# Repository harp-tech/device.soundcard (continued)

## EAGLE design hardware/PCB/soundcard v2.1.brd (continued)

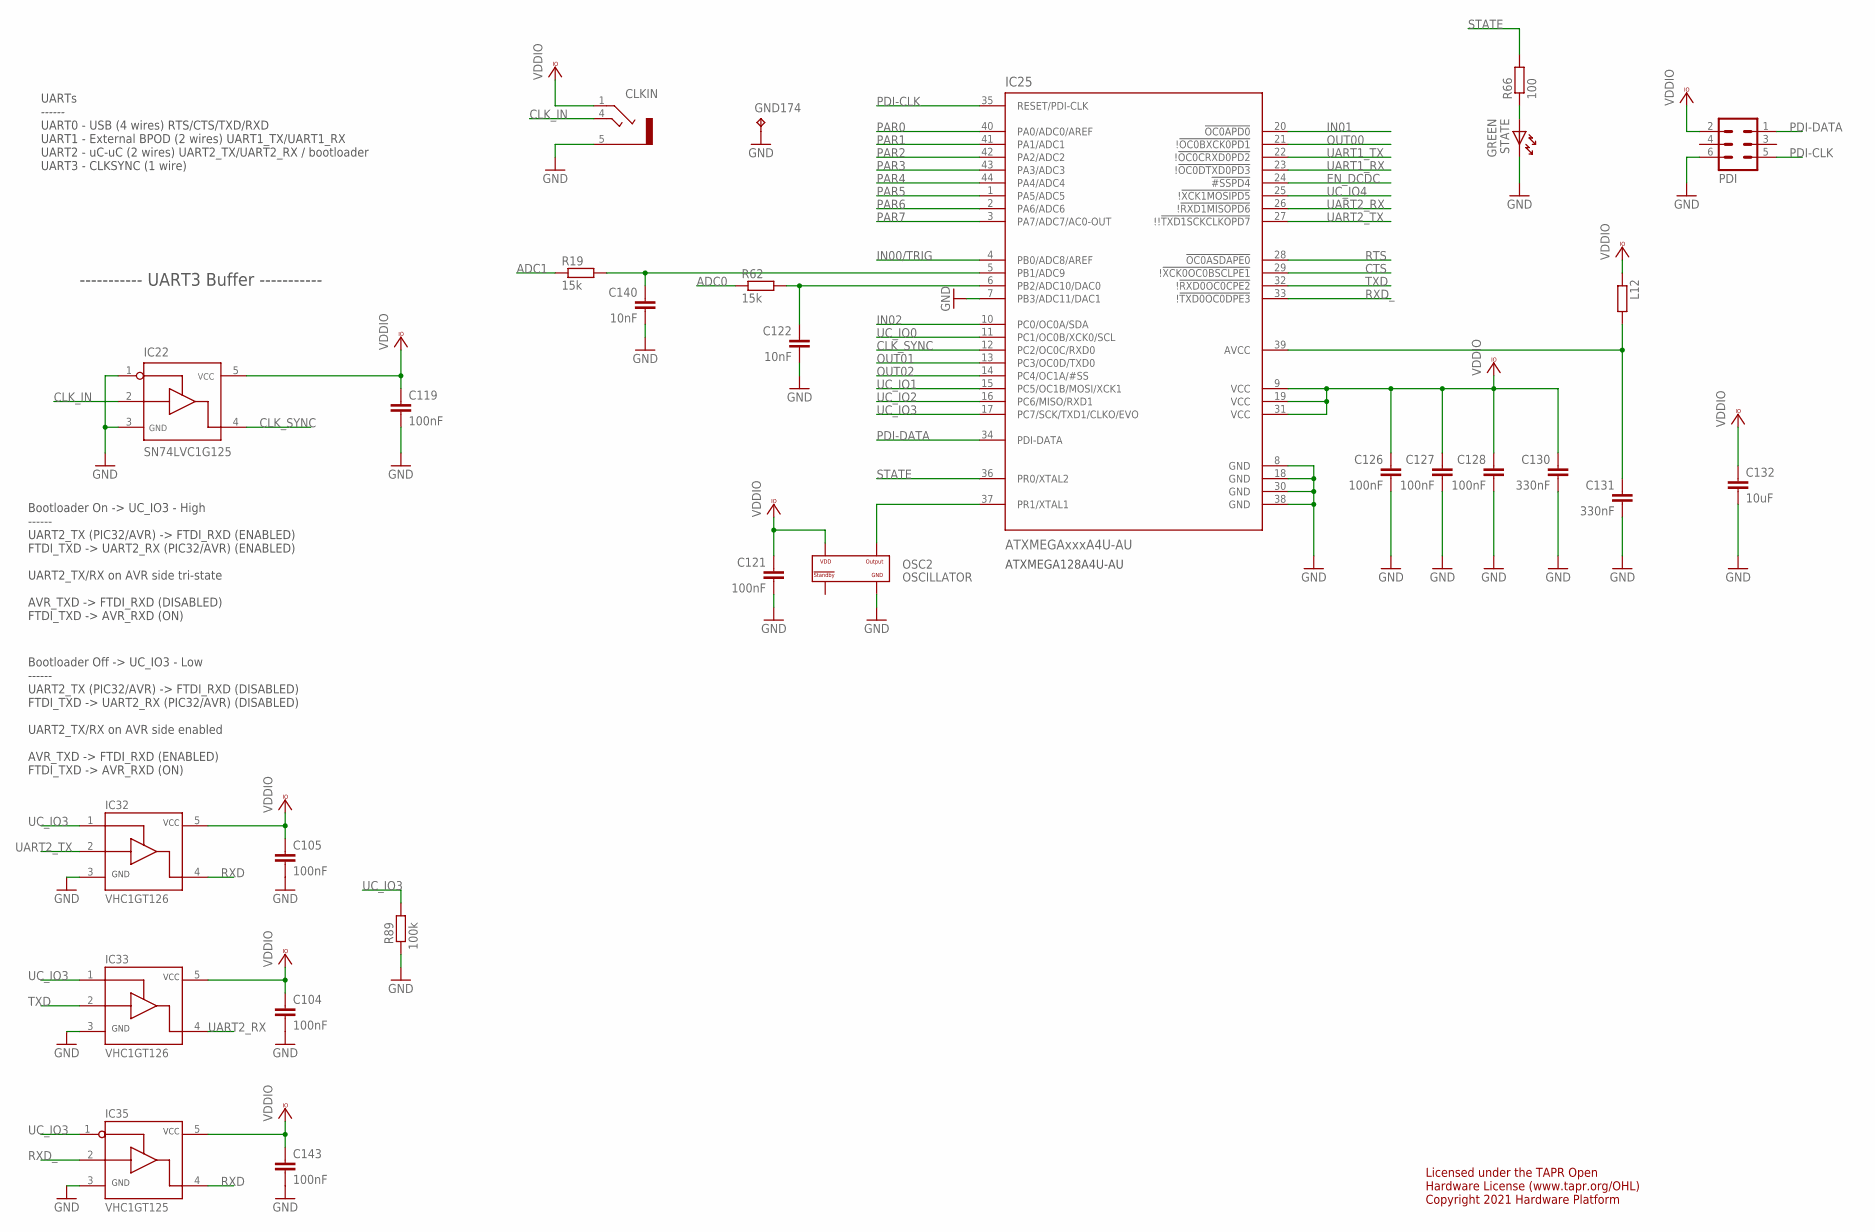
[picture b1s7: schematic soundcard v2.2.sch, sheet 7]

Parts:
C104, C105, C119, C121, C126, C127, C128, C143: 100nF; C0402
C122, C140: 10nF; C0402
C130, C131: 330nF; C0402
C132: 10uF; C0603
CLKIN: STEREO_JACK; 35RASMT2BHNTRX
GND174: TP; TP_1
IC22: SN74LVC1G125; SOT23-5
IC25: ATXMEGAxxxA4U-AU; QFP80P1200X1200X120-44N
IC32, IC33: VHC1GT126; SC-70-5
IC35: VHC1GT125; SC-70-5
L12: ???; R0805
OSC2: OSCILLATOR; OSCILLATOR_3.2X2.5
PDI: MA03-2
R19, R62: 15k; R0402
R66: 100; R0402
R89: 100k; R0402
STATE: GREEN; LED_HAND

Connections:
A+3V3: C131.1, IC25.39 (AVCC), L12.2
ADC0: R62.1; also elsewhere on the board
ADC1: R19.1; also elsewhere on the board
CLK_IN: CLKIN.4, IC22.2
CLK_SYNC: IC22.4, IC25.12 (PC2/OC0C/RXD0)
CTS: IC25.29 (!!XCK0OC0BSCLPE1); also elsewhere on the board
EN_DCDC: IC25.24 (!#SSPD4); also elsewhere on the board
GND: C104.2, C105.2, C119.2, C121.2, C122.2, C126.2, C127.2, C128.2, C130.2, C131.2, C132.2, C140.2, C143.2, CLKIN.5, GND174.TP, IC22.1, IC22.3, IC25.7 (PB3/ADC11/DAC1), IC25.8 (GND), IC25.18 (GND), IC25.30 (GND), IC25.38 (GND), IC32.3 (GND), IC33.3 (GND), IC35.3 (GND), OSC2.P$2 (GND), PDI.6, R89.2, STATE.K; also elsewhere on the board
IN00/TRIG: IC25.4 (PB0/ADC8/AREF); also elsewhere on the board
IN01: IC25.20 (!OC0APD0); also elsewhere on the board
IN02: IC25.10 (PC0/OC0A/SDA); also elsewhere on the board
unnamed: C140.1, IC25.5 (PB1/ADC9), R19.2
unnamed: C122.1, IC25.6 (PB2/ADC10/DAC0), R62.2
unnamed: R66.1, STATE.A
OSC1: IC25.37 (PR1/XTAL1), OSC2.P$3 (OUTPUT)
OUT00: IC25.21 (!!OC0BXCK0PD1); also elsewhere on the board
OUT01: IC25.13 (PC3/OC0D/TXD0); also elsewhere on the board
OUT02: IC25.14 (PC4/OC1A/#SS); also elsewhere on the board
PAR0: IC25.40 (PA0/ADC0/AREF); also elsewhere on the board
PAR1: IC25.41 (PA1/ADC1); also elsewhere on the board
PAR2: IC25.42 (PA2/ADC2); also elsewhere on the board
PAR3: IC25.43 (PA3/ADC3); also elsewhere on the board
PAR4: IC25.44 (PA4/ADC4); also elsewhere on the board
PAR5: IC25.1 (PA5/ADC5); also elsewhere on the board
PAR6: IC25.2 (PA6/ADC6); also elsewhere on the board
PAR7: IC25.3 (PA7/ADC7/AC0-OUT); also elsewhere on the board
PDI-CLK: IC25.35 (RESET/PDI-CLK), PDI.5
PDI-DATA: IC25.34 (PDI-DATA), PDI.1
RTS: IC25.28 (!OC0ASDAPE0); also elsewhere on the board
RXD: IC32.4 (OUT), IC35.4 (OUT); also elsewhere on the board
RXD_: IC25.33 (!!TXD0OC0DPE3), IC35.2 (IN)
STATE: IC25.36 (PR0/XTAL2), R66.2
TXD: IC25.32 (!!RXD0OC0CPE2), IC33.2 (IN); also elsewhere on the board
UART1_RX: IC25.23 (!!OC0DTXD0PD3)
UART1_TX: IC25.22 (!!OC0CRXD0PD2)
UART2_RX: IC25.26 (!!RXD1MISOPD6), IC33.4 (OUT); also elsewhere on the board
UART2_TX: IC25.27 (!!!TXD1SCKCLKOPD7), IC32.2 (IN); also elsewhere on the board
UC_IO0: IC25.11 (PC1/OC0B/XCK0/SCL); also elsewhere on the board
UC_IO1: IC25.15 (PC5/OC1B/MOSI/XCK1); also elsewhere on the board
UC_IO2: IC25.16 (PC6/MISO/RXD1); also elsewhere on the board
UC_IO3: IC25.17 (PC7/SCK/TXD1/CLKO/EVO), IC32.1 (OE), IC33.1 (OE), IC35.1 (!OE), R89.1; also elsewhere on the board
UC_IO4: IC25.25 (!!XCK1MOSIPD5); also elsewhere on the board
VCCIO: C104.1, C105.1, C119.1, C121.1, C126.1, C127.1, C128.1, C130.1, C132.1, C143.1, CLKIN.1, IC22.5, IC25.9 (VCC), IC25.19 (VCC), IC25.31 (VCC), IC32.5 (VCC), IC33.5 (VCC), IC35.5 (VCC), L12.1, OSC2.P$4 (VDD), PDI.2; also elsewhere on the board

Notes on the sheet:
UARTs ------ UART0 - USB (4 wires) RTS/CTS/TXD/RXD UART1 - External BPOD (2 wires) UART1_TX/UART1_RX UART2 - uC-uC (2 wires) UART2_TX/UART2_RX / bootloader UART3 - CLKSYNC (1 wire)
----------- UART3 Buffer -----------
ATXMEGA128A4U-AU
Bootloader On -> UC_IO3 - High ------ UART2_TX (PIC32/AVR) -> FTDI_RXD (ENABLED) FTDI_TXD -> UART2_RX (PIC32/AVR) (ENABLED) UART2_TX/RX on AVR side tri-state AVR_TXD -> FTDI_RXD (DISABLED) FTDI_TXD -> AVR_RXD (ON)
Bootloader Off -> UC_IO3 - Low ------ UART2_TX (PIC32/AVR) -> FTDI_RXD (DISABLED) FTDI_TXD -> UART2_RX (PIC32/AVR) (DISABLED) UART2_TX/RX on AVR side enabled AVR_TXD -> FTDI_RXD (ENABLED) FTDI_TXD -> AVR_RXD (ON)
Licensed under the TAPR Open Hardware License (www.tapr.org/OHL) Copyright 2021 Hardware Platform

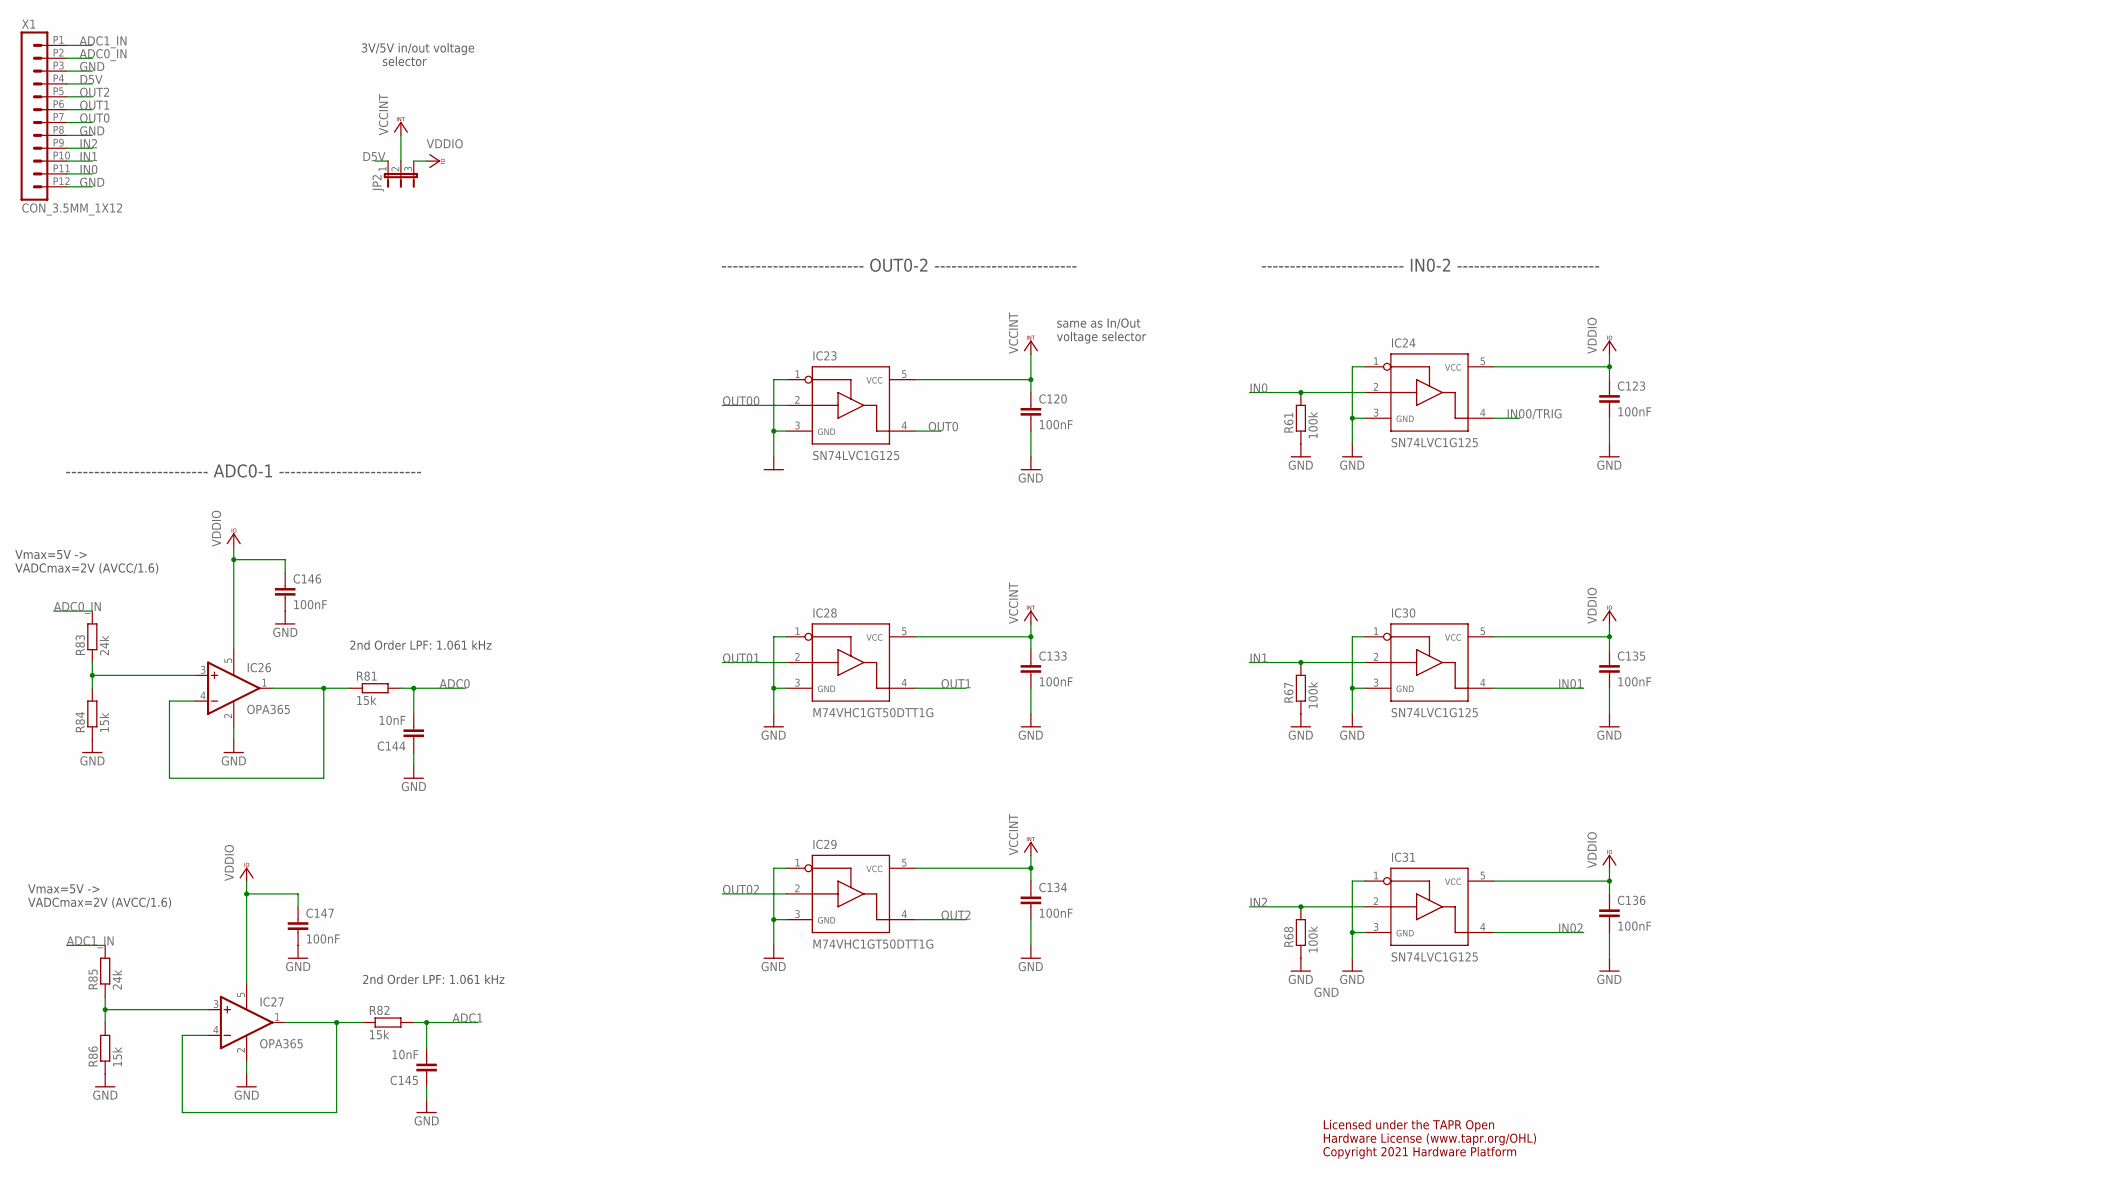
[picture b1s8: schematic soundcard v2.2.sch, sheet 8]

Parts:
C120, C123, C133, C134, C135, C136, C146, C147: 100nF; C0402
C144, C145: 10nF; C0402
IC23, IC24, IC30, IC31: SN74LVC1G125; SOT23-5
IC26, IC27: OPA365; SOT23-5
IC28, IC29: M74VHC1GT50DTT1G; SOT23-5
JP2: JP2E; JP2
R61, R67, R68: 100k; R0402
R81, R82, R84, R86: 15k; R0402
R83, R85: 24k; R0402
X1: CON_3.5MM_1X12

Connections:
ADC0: C144.2, R81.2; also elsewhere on the board
ADC0_IN: R83.2, X1.P2 (2)
ADC1: C145.2, R82.2; also elsewhere on the board
ADC1_IN: R85.2, X1.P1 (1)
GND: C120.2, C123.2, C133.2, C134.2, C135.2, C136.2, C144.1, C145.1, C146.2, C147.2, IC23.1, IC23.3, IC24.1, IC24.3, IC26.2 (V-), IC27.2 (V-), IC28.1, IC28.3, IC29.1, IC29.3, IC30.1, IC30.3, IC31.1, IC31.3, R61.2, R67.2, R68.2, R84.1, R86.1, X1.P3 (3), X1.P8 (8), X1.P12 (12); also elsewhere on the board
IN0: IC24.2, R61.1, X1.P11 (11)
IN00/TRIG: IC24.4; also elsewhere on the board
IN1: IC30.2, R67.1, X1.P10 (10)
IN01: IC30.4; also elsewhere on the board
IN02: IC31.4; also elsewhere on the board
IN2: IC31.2, R68.1, X1.P9 (9)
unnamed: IC26.1 (OUT), IC26.4 (-IN), R81.1
unnamed: IC27.1 (OUT), IC27.4 (-IN), R82.1
unnamed: IC26.3 (+IN), R83.1, R84.2
unnamed: IC27.3 (+IN), R85.1, R86.2
OUT00: IC23.2; also elsewhere on the board
OUT0: IC23.4, X1.P7 (7)
OUT01: IC28.2; also elsewhere on the board
OUT1: IC28.4, X1.P6 (6)
OUT02: IC29.2; also elsewhere on the board
OUT2: IC29.4, X1.P5 (5)
VCCINT: C120.1, C133.1, C134.1, IC23.5, IC28.5, IC29.5, JP2.2
VCCIO: C123.1, C135.1, C136.1, C146.1, C147.1, IC24.5, IC26.5 (V+), IC27.5 (V+), IC30.5, IC31.5, JP2.3; also elsewhere on the board

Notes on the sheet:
3V/5V in/out voltage selector
same as In/Out voltage selector
Licensed under the TAPR Open Hardware License (www.tapr.org/OHL) Copyright 2021 Hardware Platform
2nd Order LPF: 1.061 kHz
Vmax=5V -> VADCmax=2V (AVCC/1.6)
------------------------- ADC0-1 -------------------------
------------------------- OUT0-2 -------------------------
------------------------- IN0-2 -------------------------

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
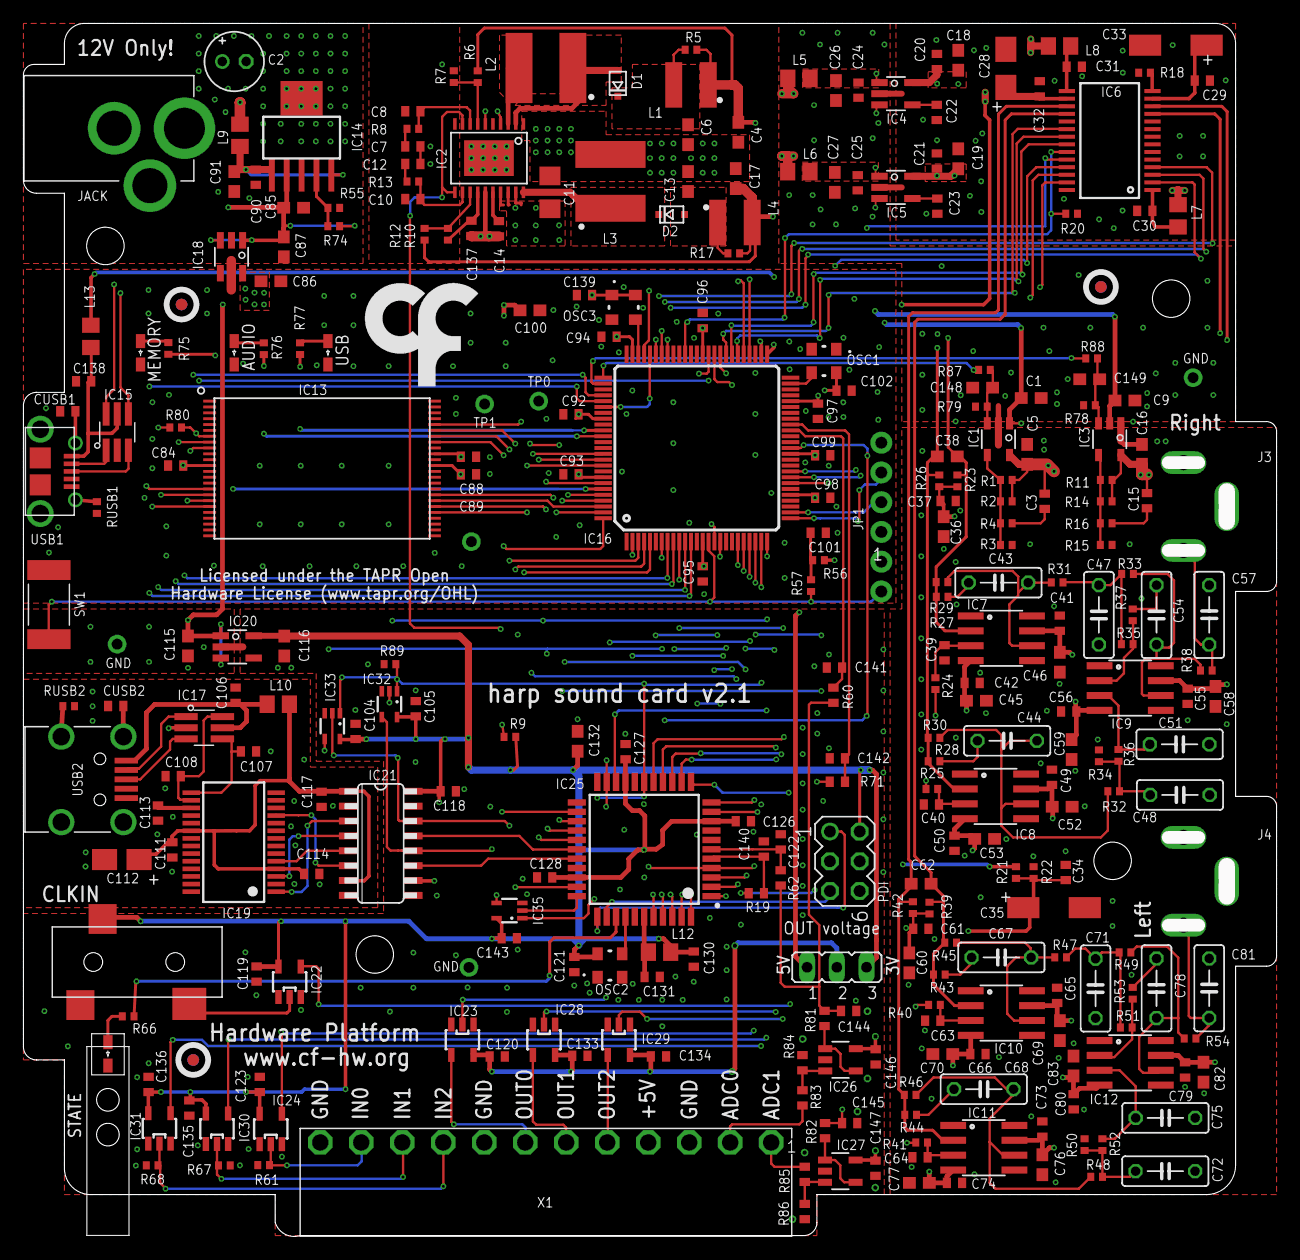
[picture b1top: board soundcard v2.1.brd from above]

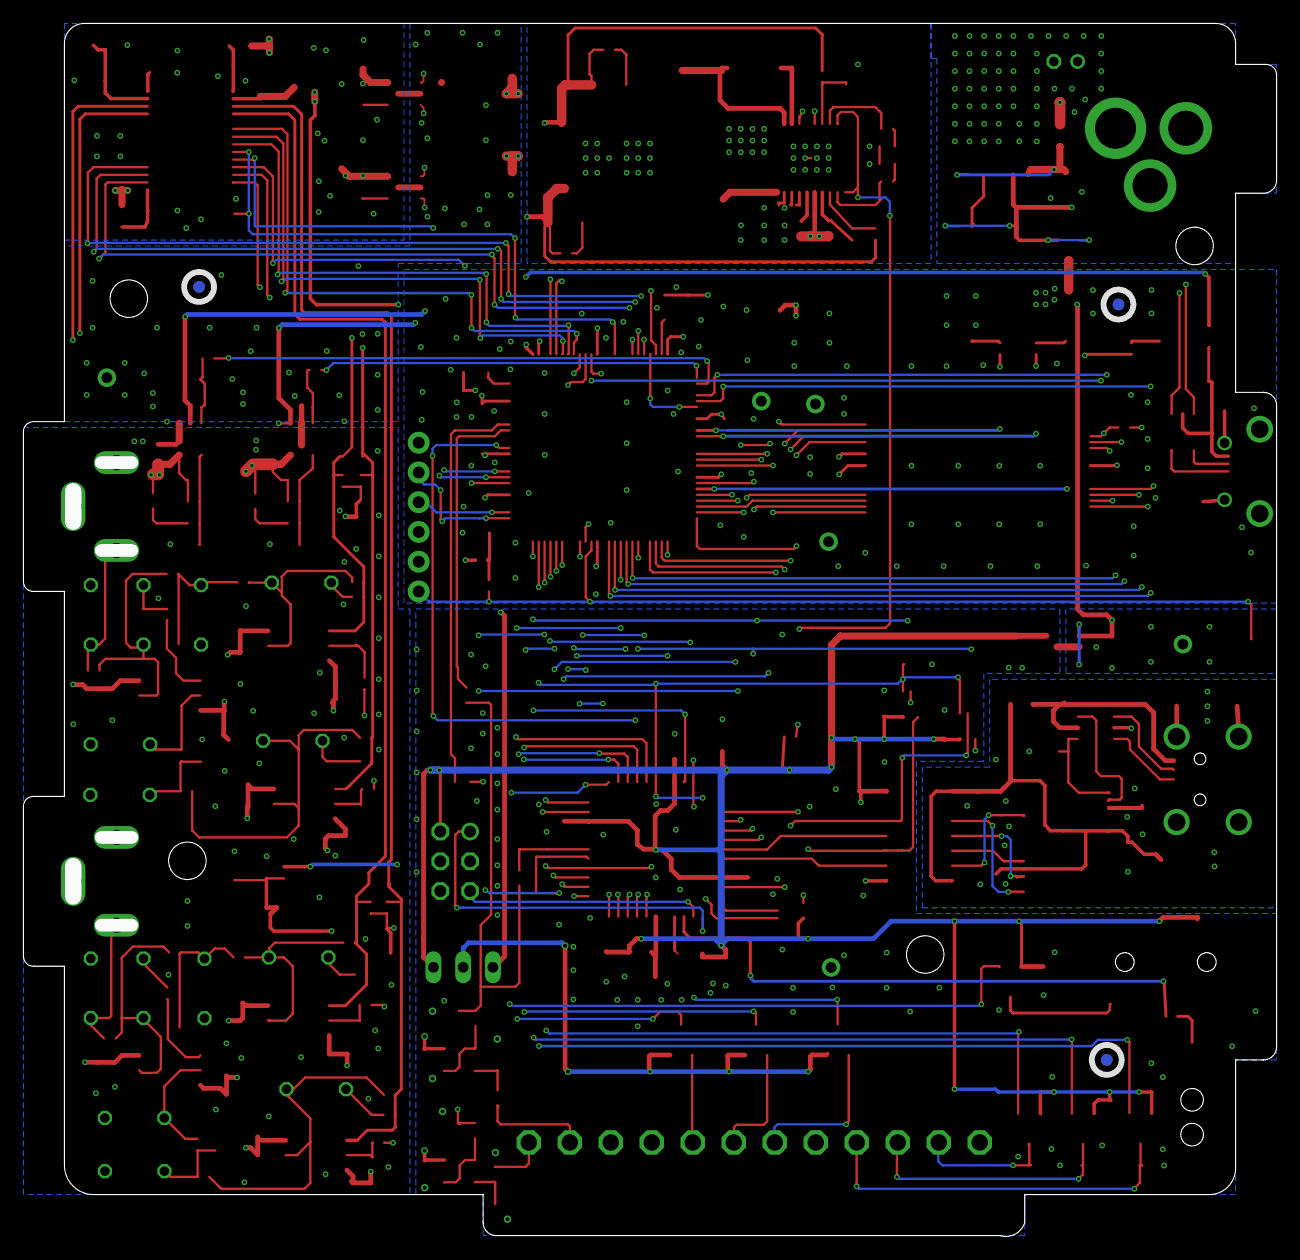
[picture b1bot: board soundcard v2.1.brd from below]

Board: 4 copper layers, 107.0 x 103.6 mm, 307 parts (3 on the bottom side), 190 nets.

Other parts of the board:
U$1: LED_PIPE_7513D2-L
U$2: LOGO_6
U$6, U$8, U$10, U$11, U$12, U$13: FIDUCIAL

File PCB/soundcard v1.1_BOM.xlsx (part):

Board | Part(s) | Quantity | Description | Distributor | Part. No.
 | IC1 | 1 | IC REG LINEAR 200MA TSOT23-5 | Digikey | ADP7118AUJZ-R7CT-ND
 | IC2 | 1 | IC REG BST SEPIC INV ADJ 20TSSOP | Digikey | ADP5070AREZ-R7CT-ND
 | IC3 | 1 | IC REG LINEAR 200MA 5TSOT | Digikey | ADP7182AUJZ-R7CT-ND
 | IC4, IC5 | 2 | IC REG LINEAR 5V 200MA 8SOIC | Digikey | ADP3303ARZ-5-ND
 | IC6 | 1 | IC DAC AUDIO MULTIBIT 28-SSOP | Digikey | AD1955ARSZ-ND
 | IC7, IC8, IC9, IC10, IC11, IC12 | 6 | IC OPAMP GP 110MHZ 8SOIC | Digikey | AD797BRZ-ND
 | IC13 | 1 | IC FLASH 2GBIT 48TSOP | Digikey | 1274-1040-ND‎
 | IC14, IC32 | 2 | IC REG LIN POS ADJ 1A SOT223-6 | Digikey | 296-39489-1-ND
 | IC15, IC17 | 2 | TVS DIODE 5.25VWM 17VC SOT23-6 | Digikey | 497-5235-1-ND
 | IC16 | 1 | IC MCU 32BIT 2MB FLASH 100TQFP | Digikey | PIC32MZ2048EFM100-I/PF
 | IC19 | 1 | IC USB FS SERIAL UART 28-SSOP | Digikey | 768-1007-1-ND
 | IC18, IC20 | 2 | IC REG LINEAR 3.3V 250MA SOT23 | Digikey | 296-38557-1-ND
 | IC21 | 1 | DGTL ISO 3.75KV GEN PURP 16SOIC | Digikey | 336-2092-5-ND
 | IC22, IC24, IC30, IC31 | 4 | IC BUS BUFF TRI-ST N-INV SOT23-5 | Digikey | 296-11603-1-ND
 | IC23, IC28, IC29 | 3 | IC BUFF CMOS LVL/SFTR N-I 5TSOP | Digikey | M74VHC1GT50DTT1GOSCT-ND
 | IC25 | 1 | IC MCU 8BIT 128KB FLASH 44TQFP | Digikey | ATXMEGA128A4U-AU-ND
 | IC26 | 1 | DGTL ISO 2.5KV GEN PURP 16SOIC | Digikey | 336-2568-ND
 | IC27 | 1 | IC DVR/RCVR RS-485 3.3V 8-SOIC | Digikey | 296-19626-1-ND
 | IC33, IC34 | 2 | IC BUFFER NON-INVERT 5.5V SC88A OE | Digikey | M74VHC1GT126DF2GOSCT-ND
 | IC35 | 1 | IC BUFFER NON-INVERT 5.5V SC88A !OE | Digikey | M74VHC1GT125DF2GOSCT-ND
 | IC37, IC38 | 2 | Amplificadores operacionais - Amp Op 2.2V 50MHz Low Noise Single Supply | Mouser | 595-OPA365AIDBVR
 | R17 | 1 | RES SMD 5.36Ω 1% 0402 | Digikey | 541-5.36LLCT-ND
 | R5 | 1 | RES SMD 6.04Ω 1% 0402 | Digikey | 541-6.04LLCT-ND
 | R69, R70 | 2 | RES SMD 33Ω 1% 0402 | Digikey | P33.0LCT-ND
 | R66 | 1 | RES SMD 68Ω 1% 0402 | Digikey | P68.0LCT-ND
 | R57, R63 | 2 | RES SMD 1kΩ 1% 0402 | Digikey | P1.00KLCT-ND
 | R10 | 1 | RES SMD 2.8kΩ 1% 0402 | Digikey | P2.80KLCT-ND
 | R75, R76, R77 | 3 | RES SMD 2.05kΩ 1% 0402 | Digikey | P2.05KLCT-ND
 | R19, R55, R60, R62, R71, R72, R80 | 7 | RES SMD 3.16kΩ 1% 0402 | Digikey | P3.16KLCT-ND
 | R7 | 1 | RES SMD 3.57kΩ 1% 0402 | Digikey | P3.57KLCT-ND
 | R13 | 1 | RES SMD 5.76kΩ 1% 0402 | Digikey | P5.76KLCT-ND
 | R8 | 1 | RES SMD 8.45kΩ 1% 0402 | Digikey | P8.45KLCT-ND
 | R73, R74 | 2 | RES SMD 9.76kΩ 1% 0402 | Digikey | P9.76KLCT-ND
 | R3, R4, R15, R16, R56, R81, R82 | 7 | RES SMD 10kΩ 1% 0402 | Digikey | P10.0KLCT-ND
 | R84, R86 | 2 | RES SMD 16kΩ 1% 0402 | Digikey | P16.0KLCT-ND
 | R83, R85 | 2 | RES SMD 24kΩ 1% 0402 | Digikey | P24.0KLCT-ND
 | R12 | 1 | RES SMD 54.9kΩ 1% 0402 | Digikey | P54.9KLCT-ND
 | R6 | 1 | RES SMD 63.4kΩ 1% 0402 | Digikey | P63.4KLCT-ND
 | R9, R20, R61, R67, R68, R78, R79, R87, R88, R89 | 8 | RES SMD 100kΩ 5% 0402 | Digikey | P100KJCT-ND
 | R11 | 1 | RES SMD 150kΩ 1% 0402 | Digikey | P150KLCT-ND
 | R1, R2 | 2 | RES SMD 180kΩ 1% 0402 | Digikey | P180KLCT-ND
 | R14 | 1 | RES SMD 215kΩ 1% 0402 | Digikey | P215KLCT-ND
 | RUSB1, RUSB2 | 2 | RES SMD 1MΩ 5% 0402 | Digikey | P17211CT-ND
 | R27, R28, R37, R43, R44, R53 | 6 | RES TH 100Ω 1% Axial | Digikey | 100XBK-ND
 | R33, R34, R49, R50 | 4 | RES TH 226Ω 0.1% Axial | Mouser | 66-RC55LF-D-226
 | R35, R36, R51, R52 | 4 | RES TH 324Ω 1% Axial | Digikey | 324XBK-ND
 | R38, R54 | 2 | RES TH 332Ω 1% Axial | Digikey | 332XBK-ND
 | R31, R32, R47, R48 | 4 | RES TH 681Ω 0.1% Axial | Mouser | 66-RC55LF-D-681
 | R24, R25, R40, R41 | 4 | RES TH 806Ω 1% Axial | Digikey | 806XBK-ND
 | R23, R26, R29, R30, R39, R42, R45, R46 | 8 | RES TH 2kΩ 0.1% Axial | Mouser | 756-RC55Y-2K0BI
 | R21 | 1 | RES TH 2.21kΩ 1% Axial | Mouser | 2.21KXBK-ND
 | R18 | 1 | RES TH 2.49kΩ 1% Axial | Digikey | 2.49KXBK-ND
 | R22 | 1 | RES TH 2.80kΩ 1% Axial | Digikey | 2.80KXBK-ND
 | C8, C107, C108 | 3 | CAP SMD CER 47pF 50V ±5% C0G 0402 | Digikey | 490-8206-1-ND
 | C10 | 1 | CAP SMD CER 68pF 50V ±5% C0G 0402 | Digikey | 490-8219-1-ND‎
 | C38, C62 | 2 | CAP SMD CER 100pF 50V ±5% C0G 0603 | Digikey | 709-1147-1-ND
 | C7 | 1 | CAP SMD CER 820pF 50V ±5% C0G 0402 | Digikey | 445-8064-1-ND
 | CUSB1, CUSB2 | 2 | CAP SMD CER 4.7nF 50V ±10% X7R 0402 | Digikey | 490-4915-1-ND
 | C12 | 1 | CAP SMD CER 6.8nF 50V ±10% X7R 0402 | Digikey | 1276-1585-1-ND
 | C22, C23 | 2 | CAP SMD CER 10nF 50V ±10% X7R 0402 | Digikey | 490-4762-1-ND
 | C144, C145 | 2 | CAP SMD CER 15nF 16V ±10% X7R 0402 | Digikey | 1276-1524-1-ND
 | C15, C20, C21, C24, C25, C29, C30, C31, C32, C84, C88, C89, C90, C92, C93, C94,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 | 55 | CAP SMD CER 100nF 25V ±10% X5R 0402 | Digikey | 1276-1043-1-ND
 | C130, C131 | 2 | CAP SMD CER 330nF 10V ±10% X5R 0402 | Digikey | 1276-6665-1-ND
 | C3, C14, C137 | 3 | CAP SMD CER 1uF 25V ±10% X5R 0402 | Digikey | 1276-1445-1-ND
 | C4, C6, C13, C17, C148, C149 | 6 | CAP SMD CER 1uF 25V ±10% X5R 0603 | Digikey | 490-16608-1-ND
 | C1, C5, C9, C16 | 4 | CAP SMD CER 2.2uF 35V ±10% X5R 0603 | Digikey | 445-8025-1-ND
 | C112 | 1 | CAP SMD TAN 4.7uF 6.3V ±10% 1206 | Digikey | 399-9717-1-ND
 | C11 | 1 | CAP SMD CER 10uF 25V ±20% X5R 1206 | Digikey | 445-8806-1-ND
 | C18, C19, C26, C27, C85, C86, C87, C91, C100, C103, C110, C115, C116, C132 | 14 | CAP SMD CER 10uF 25V ±20% X5R 0603 | Digikey | 445-9015-1-ND
 | C28 | 1 | CAP SMD TAN 10uF 16V ±20% 1411 | Digikey | 399-8446-1-ND
 | C33 | 1 | CAP SMD TAN 47uF 16V ±10% 2312 | Digikey | 399-9763-1-ND
 | C43, C44, C67, C68 | 4 | CAP TH FILM 100pF 100V ±5% PP Radial | Mouser | 505-FKP2100/100/5
 | C51, C54, C75, C78 | 4 | CAP TH FILM 2.7nF 100V ±2.5% PP Radial | Mouser | 505-FKP2D012701DHA00
 | C57, C81 | 2 | CAP TH FILM 3.9nF 63V ±5% PP Radial | Mouser | 505-FKP2-3900632.5A
 | C47, C48, C71, C72 | 4 | CAP TH FILM 5.6nF 63V ±5% PP Radial | Mouser | 505-FKP2C015601DHC00
 | C34, C37, C39, C40, C41, C42, C49, C50, C55, C56, C61, C63, C64, C65, C66, C73,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 | 19 | CAP TH FILM 100nF 100V ±5% Poly Radial | Mouser | BFC237022104
 | C36, C45, C46, C52, C53, C58, C59, C60, C69, C70, C76, C77, C82, C83 | 14 | CAP TH ELEC 4.7uF 35V ±20% Alum Radial | Digikey | 493-1847-ND
 | C35 | 1 | CAP TH ELEC 47uF 16V ±20% Alum Radial | Digikey | P11196-ND
 | C2 | 1 | CAP TH ELEC 68uF 25V ±20% Alum Radial | Digikey | P14412-ND
 | L1, L4 | 2 | IND SMD 1.5uH 2.2A ±20% | Mouser | 994-LPS4012-152MRB
 | L2 | 1 | IND SMD 3.3uH 1.35A ±20% | Mouser | 994-LPS6225-332MRB
 | L3 | 1 | IND SMD 15uH 1.2A ±20% | Mouser | 994-LPS6225-153MRB
 | L5, L6, L7, L8, L9, L11 | 6 | FERRITE BEAD 600Ω 500mA 300mΩ 0805 | Digikey | 240-2399-1-ND
 | L12 | 1 | FERRITE BEAD 330Ω 1.5A 70mΩ 0603 | Digikey | 490-3997-1-ND
 | L10, L13 | 2 | FERRITE BEAD 70Ω 1.5A 50mΩ 0805 | Digikey | 240-2389-1-ND
 | D1, D2 | 2 | DIODE SCHOTTKY 30V 1A SOD323 | Digikey | BAS3010A03WE6327HTSA1CT-ND
 | STATE | 1 | LED GREEN 0603 SMD | Digikey | 751-1176-1-ND
 | MEMORY, AUDIO, USB | 3 | LED RED 0603 SMD | Digikey | 751-1182-1-ND
 | OSC1 | 1 | OSC MEMS 24.000MHZ CMOS | Digikey | 535-11728-1-ND
 | OSC2 | 1 | OSC MEMS 32.0000MHZ CMOS | Digikey | DSC1001CI5-032.0000-ND
 | OSC3 | 1 | OSC MEMS 24.576MHZ CMOS | Digikey | 535-11156-1-ND
 | USB2 | 1 | RECEPT MINI USB2.0 5POS | Digikey | H2960CT-ND
 | USB1 | 1 | CONN RCPT USB MICRO B SMD | Digikey | H125272CT-ND
 | CLKIN | 1 | JACK STEREO 3.5MM SMD R/A | Digikey | SC1489-1-ND
 | JP2 | 1 | CONN HEADER 3POS .100 STR | Digikey | 609-3470-ND
 | JP1 | 1 | CONN HEADER 6POS .100 STR | Digikey | 609-3256-ND
 | PDI | 1 | CONN HEADER 6POS .100 STR | Digikey | 609-3210-ND
 | IN, OUT | 2 | CONN BNC JACK R/A 50 OHM | Digikey | A32244-ND
 | J1, J2 | 2 | CONN MOD JACK 8P8C R/A UNSHLD | Digikey | A105009CT-ND
 | J3 | 1 | CONN RCA JACK MONO 3.2MM R/A RED | Digikey | SC1853-ND
 | J4 | 1 | CONN RCA JACK MONO 3.2MM R/A BLACK | Digikey | SC1852-ND
 | JACK | 1 | CC PCB 2.1MM | Mouser | 163-179PH-EX
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
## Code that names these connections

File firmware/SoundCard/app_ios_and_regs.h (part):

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/************************************************************************/
/* Definition of output pins                                            */
/************************************************************************/
// PAR0                   Description: Digital bus pin 0
// PAR1                   Description: Digital bus pin 1
// PAR2                   Description: Digital bus pin 2
// PAR3                   Description: Digital bus pin 3
// PAR4                   Description: Digital bus pin 4
// PAR5                   Description: Digital bus pin 5
// PAR6                   Description: Digital bus pin 6
// PAR7                   Description: Digital bus pin 7
// DOUT0                  Description: Digital output 0
// DOUT1                  Description: Digital output 1
// DOUT2                  Description: Digital output 2
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#define ADD_REG_ATTENUATION_START           37 // U16    Specifies attenuation and simultaneously starts the sound index or frequency [Index] [Att L] [Att R].
#define ADD_REG_DELETE_SOUND                38 // U8     Deletes the sound stored at the specified index.
#define ADD_REG_DELETE_ALL_SOUNDS           39 // U8     Deletes all sounds stored in the device when the written value is non-zero.
#define ADD_REG_INPUT_STATE                 40 // U8     Reports the state of the digital inputs. Events are sent only for inputs configured in Digital mode.
#define ADD_REG_CONFIGURE_DI0               41 // U8     Specifies the operation mode of the digital input 0 (DI0).
#define ADD_REG_CONFIGURE_DI1               42 // U8     Specifies the operation mode of the digital input 1 (DI1).
#define ADD_REG_START_ON_DI0                43 // U16    Specifies the sound index or frequency to start when triggering DI0, following the same rules as Start.
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#define ADD_REG_OUTPUT_SET                  58 // U8     Sets the specified digital output lines.
#define ADD_REG_OUTPUT_CLEAR                59 // U8     Clears the specified digital output lines.
#define ADD_REG_OUTPUT_TOGGLE               60 // U8     Toggles the specified digital output lines.
#define ADD_REG_OUTPUT_STATE                61 // U8     Writes the state of all digital output lines.
#define ADD_REG_RESERVED8                   62 // U8     Reserved for future use.
#define ADD_REG_RESERVED9                   63 // U8     Reserved for future use.
#define ADD_REG_ENABLE_ADC_CONTROL_STATE    64 // U8     Specifies whether the ADC control state is reported, sampled at 1 kHz.
#define ADD_REG_ADC_CONTROL_STATE           65 // U16    Reports sampled analog input data and current sound parameters.
#define ADD_REG_CONFIGURE_ADC0              66 // U8     Specifies the operation mode of analog input ADC0 (not implemented yet).
#define ADD_REG_CONFIGURE_ADC1              67 // U8     Specifies the operation mode of analog input ADC1 (not implemented yet).
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
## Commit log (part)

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2018-10-15 Created README.md.
2018-10-15 Created .gitignore.
2018-10-15 Added the firmware code for the sound card's controller (8 bits processor).
2018-10-15 Added the firmware code for the sound card's 32 bits processor.
2018-10-15 Added the C# code for the interface between the computer and the sound card's 32 bits processor.
2018-10-15 Added PCB and case files.
2018-10-18 Updated the errors list.
2018-10-18 Minor corrections and clean up.
2018-10-18 Added ability to read the metadata from the sound card memory.
2018-10-19 Added output string and updated the metadata's file text.
2018-10-22 Added ability to save a description file up to 512 bytes in the device's memory.
2018-10-22 Updated assembly information.
2018-11-22 Corrected error that was crashing DMA when the number of samples was equal to 2048 x N + 2. Minor cleanup.
2018-12-05 Updated comments regarding files indexes.
2018-12-14 Implemented the comunication between PIC32 and ATXMEGA. Some clean up.
2018-12-14 Added and renamed registers. Some clean up.
2018-12-14 Added first code for the analog inputs.
2018-12-20 Re-coded the BPod comunication to use callbacks. Some clean up of the app.c file.
2019-02-14 Fixed #1 and added ability to ignore user inputs (for debug purposes).
2019-02-14 Added comments and ability to ignore user inputs (for debug purposes).
2019-02-14 Added 3 sound files to help during debug.
2019-02-20 Added ability to receive new sound data while playing a sound.
2019-02-25 Minor corrections and slight performance improvements.
2019-02-25 Updated version to 1.0.1.
2019-02-27 Prepared firmware for bootloader compatibility.
2019-02-27 Added bootloader raw files.
2019-02-28 Updated .gitignore.
2019-02-28 Updated bootloader to our case and added the dependencies' package to remove all local dependencies.
2019-02-28 Added the dependencies' package to the firmware to remove all local dependencies.
2019-02-28 Removed old bootloader routines.
2019-02-28 Protected device when user sends new data and a sound is being produced with 192Ksample/sec.
2019-03-07 Implemented the Stop command in the parallel bus.
2019-03-07 Corrected the bug that did not allow to produce correct sound in the first 512 samples.
2019-03-14 Fixed #2.
2019-03-14 Implemented the ability to confirm if a command was executed (using CMD_NOT_EXEC signal).
2019-03-14 Updated some pin names.
2019-03-15 Prepared versions for release.
2019-03-19 implemented command to clean a sound index or the entire memory.
2019-03-19 Removed reset and clean up commands from the USB high speed connection. Small clean up.
2019-03-19 Replaced PCB files with the version 1.1.
2019-03-25 Added firmware licenses.
2019-03-25 Minor changes and added gerbers.
2019-03-25 Added centroids.
2019-03-26 Added BOM for assembly houses.
2019-03-26 Removed BOM for assembly houses.
2019-03-26 Minor corrections.
2019-06-19 Fixed initial "mute" bug and deleted unused functions.
2019-06-19 Added abiity to notify the ATXMEGA trough a digital line when the sound starts and stops.
2019-07-17 Removed OUT0 state machine and added the global sound_index_on.
2019-07-17 Added filter to return error if the index to play is bellow 2.
2019-07-17 Added TCP server protocol.
2019-07-17 Updated the rest of the files before the release.
2019-07-17 Updated firmware version to 2.0.
2020-05-24 Added case fabrication details.
2020-05-24 Added panel production files.
2022-01-14 Changed DIN0 edge triggering
2022-01-14 Added external trigger and event through DIN0
2022-01-14 Added CMD_INDEX to the inter processor bus
2022-01-14 Correct DOUT2 bug
2022-01-14 Remove ADC events
2022-01-14 Update Atmel Studio version
2022-01-14 Adjusted sound on latency
2022-01-14 Added CMD_INDEX
2022-01-14 Added external interrupt for future use
2022-09-23 organize PCB folder and add SB v1.1 files
2023-03-28 Take libusb dependency from nuget
2023-03-28 Add interface license
2023-03-29 Add prototype device schema and interface
2023-03-29 Avoid using less than or greater than symbols
2023-03-29 Generate symbols package
2023-03-29 Add missing bitmask and group masks
2023-07-31 Update interface to use new generators
2023-08-03 Add missing package metadata for stable release
2023-08-10 Refactor repository structure
2023-12-06 Implementation of sin generator on ATxmega
2023-12-06 Implement sin generator on PIC32
2023-12-06 Add external trigger support
2023-12-06 Sound notification prepare
2023-12-30 Update yml - firmware version
2024-01-05 Update Readme and create Assets folder
2024-02-14 Update PCB version
2024-02-29 Add citation file
2024-02-29 Fix small typos
2024-04-03 Update README formatting for docfx compatibility
2024-04-09 Update YML to comply with device meta-schema
2024-04-10 Add support for specifying which device to update
2024-04-10 Add support for specifying an optional sound name
2024-04-10 Remove unused usings and minor style changes
2024-04-10 Add operator for dynamic update of sound waveforms
2024-04-10 Ensure conversion keeps buffer dimensions
2024-04-10 Ensure only Int32 sample type is used
2024-04-10 Add support for raw binary waveform buffers
2024-04-10 Ensure uploaded waveforms are stereo
2024-04-10 Remove XML documentation from internal types
2024-05-02 Removed not used registers and updated registers' description.
2024-05-03 Removed more not used registers and created ADCx_CONF.
2024-05-03 Moved register REG_COMMANDS to position 82.
    This is needed to keep the firmware update working.
2024-06-20 Added read of the digital inputs.
2024-06-20 Implemented digital input interrupts.
2024-06-20 Changed registers to U16
2024-06-20 Correct digital output configuration.
2024-06-20 Minor correction and protect writing to the data stream register.
2024-06-20 Implemented the data stream.
2024-06-20 Moved ADC readings into interrupts.
2024-06-20 Implemented the stop command.
2024-06-20 Added pulse to digital outputs and implemented defaults.
2024-06-20 Fixed START event when sent from digital inputs.
2024-06-20 Stop frequency when goes to standby. Fix #5.
2024-07-09 Correct SoundOrFrequency type
2024-07-09 Fix digital outputs
2024-07-11 Correct typos
2024-07-11 Remove default value that causes generator to fail when casting to Enum
2024-07-11 Make not implemented registers private
2024-07-11 Add pulse duration information
2024-11-09 Fix schema source
2024-11-09 Update generators and regenerate interface
2024-11-09 Update package metadata to embed device metadata
2024-11-10 Add harp-tech as source of device schema
2025-05-16 Create basic CI/CD for interface package
2025-06-07 Remove unused local
2025-06-07 Add package README and update package build config
2025-06-07 Revert version to avoid skipping releases
2026-03-13 Allow interface to also build for net8.0
2026-03-13 Update LibUsbDotNet dependency
2026-03-13 Remove unused reset command variables
2026-03-13 Add SoundGeneration View and ViewModel
    - Pulse and Noise generation with the same options available in the old
    UI.
    - Add Phase parameter for Pulse generation
    - Add chart for generated signal (allows image export)
2026-03-13 Add SoundGeneration to main interface
2026-03-13 Add initial app
2026-03-13 Add NWaves dependency for signal generation
2026-03-13 Add converter
2026-03-13 Add ScottPlot dependency
2026-03-13 Add custom signal builders
2026-03-13 Update Solution items
2026-03-13 Add ability to play a sound of a connected SoundCard
2026-03-13 Add ability to send generated waveforms to device
2026-03-13 Adjust plot automatically on sound generation
2026-03-13 Fix issue with pure tone generation
2026-03-13 Add simple Validation rules for Pure tones generation fields
2026-03-13 Set default play sound index
2026-03-13 Add ReactiveUI.Validation dependency
2026-03-13 Update About text
2026-03-13 Update UI layout
2026-03-13 Update ports listing
2026-03-13 Update application version information
2026-03-13 Add new parameter to NSIS installer creation script
2026-03-13 Update project with UseAppHost property
2026-03-13 Change how plot auto scales
2026-03-13 Add .gitattributes
2026-03-13 Reorganize UI layout by adding Tabs for "Pure tones" and "Noise" options
2026-03-13 Add SaveToFile Command
2026-03-13 Add macOS specific information to the README
2026-03-13 Show error to user when SoundCard is not connected to send files
2026-03-13 Handle build warnings
2026-03-13 Update project settings for macOS
2026-03-13 Add import .bin file functionality
2026-03-13 Update windows installer script
2026-03-13 Parse index and sound name from imported .bin filename
2026-03-13 Update version
2026-03-13 More UI adjustments
2026-03-13 Fix issue when the user didn't select a file
2026-03-13 UI adjustments
